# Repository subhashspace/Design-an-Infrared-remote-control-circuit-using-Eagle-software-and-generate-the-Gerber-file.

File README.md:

# Design-an-Infrared-remote-control-circuit-using-Eagle-software-and-generate-the-Gerber-file.
## Exp 3: Design an Infrared remote control circuit using Eagle software
## AIM:
To design the schematic and PCB layout diagram of an Infrared remote control circuit using Eagle software.

## EQUIPMENT REQUIRED:
●	Hardware: Personal Computer (PC)<br>
●	Software: Eagle <br>
## PROCEDURE:
	Create a New Project:<br>
o	Launch EAGLE and start a new project for your PCB design.<br>
o	Within the project, create a new schematic file.<br>
	Add Components:<br>
o	Utilize the built-in libraries in EAGLE or create custom libraries if needed.<br>
o	Use the 'Add' tool to place the required components onto the schematic sheet.<br>
	Make Connections:<br>
o	Connect the components using the 'Net' tool.<br>
o	Label the nets clearly to maintain clarity and organization in your design.<br>
	Check for Errors:<br>
o	Once the schematic design is complete, perform an Electrical Rule Check (ERC) to identify and correct any errors.<br>
o	Save the schematic after confirming that no errors are present.<br>
	Switch to Board Layout:<br>
o	Click on the 'Generate/Switch to Board' button to create the PCB layout from the schematic.<br>
	Arrange Components and Route Traces:<br>
o	In the board layout editor, arrange the components to optimize space and reduce signal interference.<br>
o	Use the 'Route' tool to connect the components based on the schematic design.<br>
o	Ensure proper routing by utilizing the available editing tools in EAGLE to avoid design rule violations.<br>
	Design Rule Check (DRC):<br>
o	Perform a Design Rule Check (DRC) to ensure that the routing and layout comply with design standards and that there are no issues.<br>
o	Save the board layout after resolving any errors.<br>
	Generate Gerber Files:<br>
o	Go to File > CAM Processor and configure the CAM jobs to generate Gerber files for all PCB layers, such as copper layers, silkscreen, solder mask, and drill files.<br>
o	Verify the generated files to ensure they contain all necessary information for manufacturing.<br>
	Save Manufacturing Files:<br>
o	Save the Gerber files and any other required manufacturing files to send to your PCB manufacturer for fabrication.<br>

## THEORY:
The Infrared Remote Control Switch is a simple electronic circuit that uses an infrared (IR) receiver to detect signals from a standard TV remote and control an electrical load, such as a lamp or appliance, through a relay. At the heart of the circuit lies the CD4027 IC, which is a dual JK flip-flop. JK flip-flops are bistable multivibrators capable of storing one bit of data and toggling their state with every pulse input. In this circuit, the TSOP1738 IR receiver module is used to detect IR pulses sent by a remote control. The TSOP1738 is designed to receive 38kHz modulated infrared signals and output a demodulated digital signal that can be read by a microcontroller or logic circuit. The 2N4403 PNP transistor is used to amplify and condition the signal from the TSOP1738, ensuring a reliable trigger for the flip-flop. This type of system demonstrates the fundamental concept of remote-controlled electronics using modulated IR signals, logic circuitry, and electromechanical switching components like relays.
### Working:
When a button on the IR remote is pressed, it sends a modulated 38kHz IR signal which is received by the TSOP1738. The TSOP demodulates the signal and produces a low pulse which is fed into the base of the first 2N4403 transistor, acting as an amplifier. This transistor then provides a strong triggering signal to the CD4027 flip-flop IC, which is wired to toggle its output state with each pulse received. The output from the flip-flop then controls the base of a second 2N4403 transistor, which functions as a switch to drive a 5V relay. When the flip-flop output goes high, the transistor conducts and energizes the relay coil, turning ON the connected load. On receiving the next IR pulse, the output toggles low, deactivating the relay and turning OFF the load. An LED indicator connected in parallel with the relay provides a visual cue of the ON/OFF status. The 1N4007 diode across the relay protects the circuit from voltage spikes due to back EMF when the relay is switched OFF. This toggling operation continues every time a button on the IR remote is pressed, making it suitable for simple wireless control applications.
## CIRCUIT DIAGRAM:

## EXPECTED OUTPUT:
### Schematic diagram

### Layout diagram

## RESULT:
Thus, the schematic and PCB layout for the Infrared remote control circuit has been successfully designed using Eagle software.

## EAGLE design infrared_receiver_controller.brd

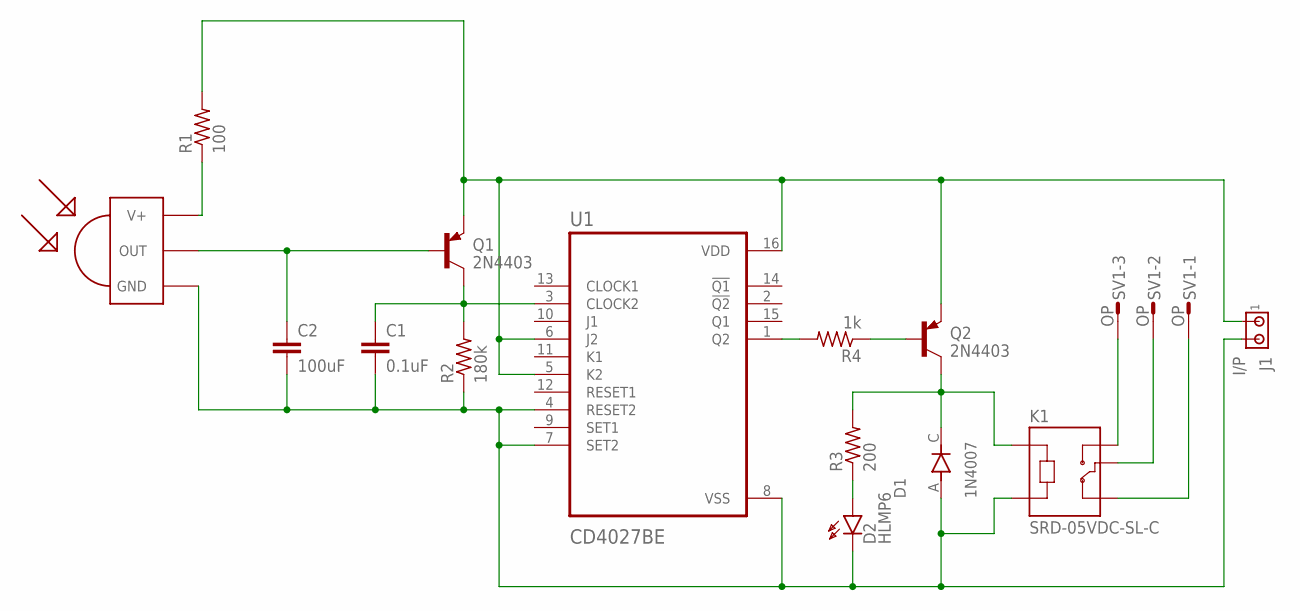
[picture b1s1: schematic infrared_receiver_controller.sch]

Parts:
C1: 0.1uF; C2.5-2
C2: 100uF; C2.5-2
D1: 1N4007; DIOAD1060W80L520D270
D2: HLMP6
J1: I/P; 10X02MTA
K1: SRD-05VDC-SL-C; RELAY_SRD-05VDC-SL-C
Q1, Q2: 2N4403; TO92
R1: 100; 0204/7
R2: 180k; 0204/7
R3: 200; 0204/7
R4: 1k; 0204/7
SV1: OP; L03P
U1: CD4027BE; DIP794W45P254L1969H508Q16
U$1: TSOP1738; TSOP17XX

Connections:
unnamed: Q2.2 (B), R4.1
unnamed: R1.1, U$1.V+
unnamed: D2.A, R3.1
unnamed: J1.1, Q1.1 (E), Q2.1 (E), R1.2, U1.5 (K2), U1.6 (J2), U1.16 (VDD)
unnamed: C2.1, Q1.2 (B), U$1.OUT
unnamed: C1.1, Q1.3 (C), R2.2, U1.3 (CLOCK2)
unnamed: C1.2, C2.2, D1.A, D2.K, J1.2, K1.A2, R2.1, U1.4 (RESET2), U1.7 (SET2), U1.8 (VSS), U$1.GND
unnamed: R4.2, U1.1 (Q2)
unnamed: D1.C, K1.A1, Q2.3 (C), R3.2
unnamed: K1.NO, SV1.3
unnamed: K1.COM, SV1.2
unnamed: K1.NC, SV1.1

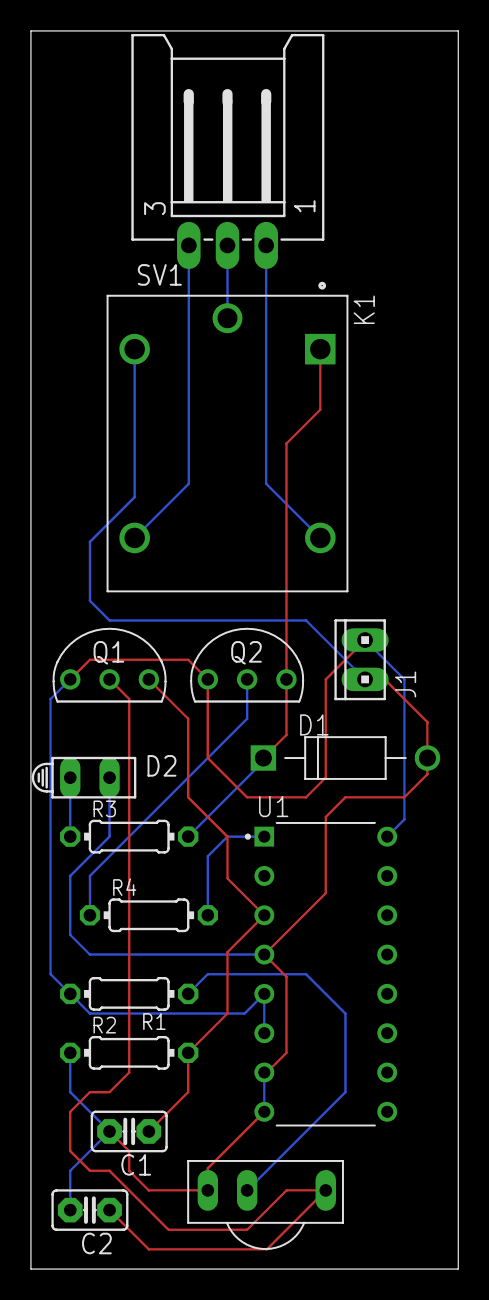
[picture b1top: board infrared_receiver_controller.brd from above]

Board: 2 copper layers, 27.6 x 80.0 mm, 15 parts (0 on the bottom side), 12 nets.
